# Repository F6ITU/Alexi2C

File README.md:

# Alexi2C

Kicad files

I2C control board interfacing 
Alexiares/Penelope input/output filter set 
with Hermes Lite 2.x & Red Pitaya 

It could also be used with a decimal/7 bits binary input for 
Hermes lite 1.0 

http://www.hermeslite.com/

This board is a fork of the DC2PD interface for the Red Pitaya
http://rz1zr.ru/files/Hermes_and_Alex_outputs.pdf

It has
been designed to 

- Control a set of Alexiares LPF and HPF filters
using the Hermes lite or Red Pitaya's I2C output (Steve KF7O or Pavel Denim's firmware).
http://pavel-demin.github.io/red-pitaya-notes/sdr-transceiver-hpsdr/

- Control a simple BCD or decimal filter (J6 output of an Hermes Lite)
In this case, the TCA9555 and the 5 pins "I2C Input" connector are not used

 === Hardware modifications===

A set of darlington (ULN2803) is used to fit the voltage 
and current requirement of both lpf and hpf boards. 

A pair of jumpers located close to the output connectors 
allow to use the "local" 12V  power rail if set, 
or any external voltage when opened. 

For hams using this board with the KF7O's Hermes Lite V1 (deprecated dev.), two connectors 
have been added to directly control the drivers in decimal mode,
thus to control a Penelope, Alexiares or an Alex SV1AL softrock based 
"Big Mobo" filter set ( or any filter 
board using negative logic band switching) 

Please note that the antenna and attenuator commands need a separate 
board if an Alex lpf/hpf filter set is already used (Pavel's firmware). 

An antenna switching board project could be downloaded and/or forked from 

https://github.com/F6ITU/Alexiares_Coax_Out

(attenuators are integrated on the HPF filter board, under design)

When using AlexI2C, Alexandrie control board, the original I2S interface

https://github.com/F6ITU/Alexandrie

should NOT be used (it seems obvious, but who knows...)

AlexI2C acts as an "almost complete" substitute of the original board and is 
dedicated to people who don't want to use Alexiares's I2S protocol.

3D image of the board are stored on this repo

Alexi2C dwn.jpg

Alexi2C up.jpg

Board's dimensions are oversized to fit the 5x10 and 10x10cm 
size of all board of the Hermes project under Kicad: 

AlexI2C

Alexandrie 

Alexiares_Coax_Out

Alexiares_HPF

Alexiares_LPF

Mentor

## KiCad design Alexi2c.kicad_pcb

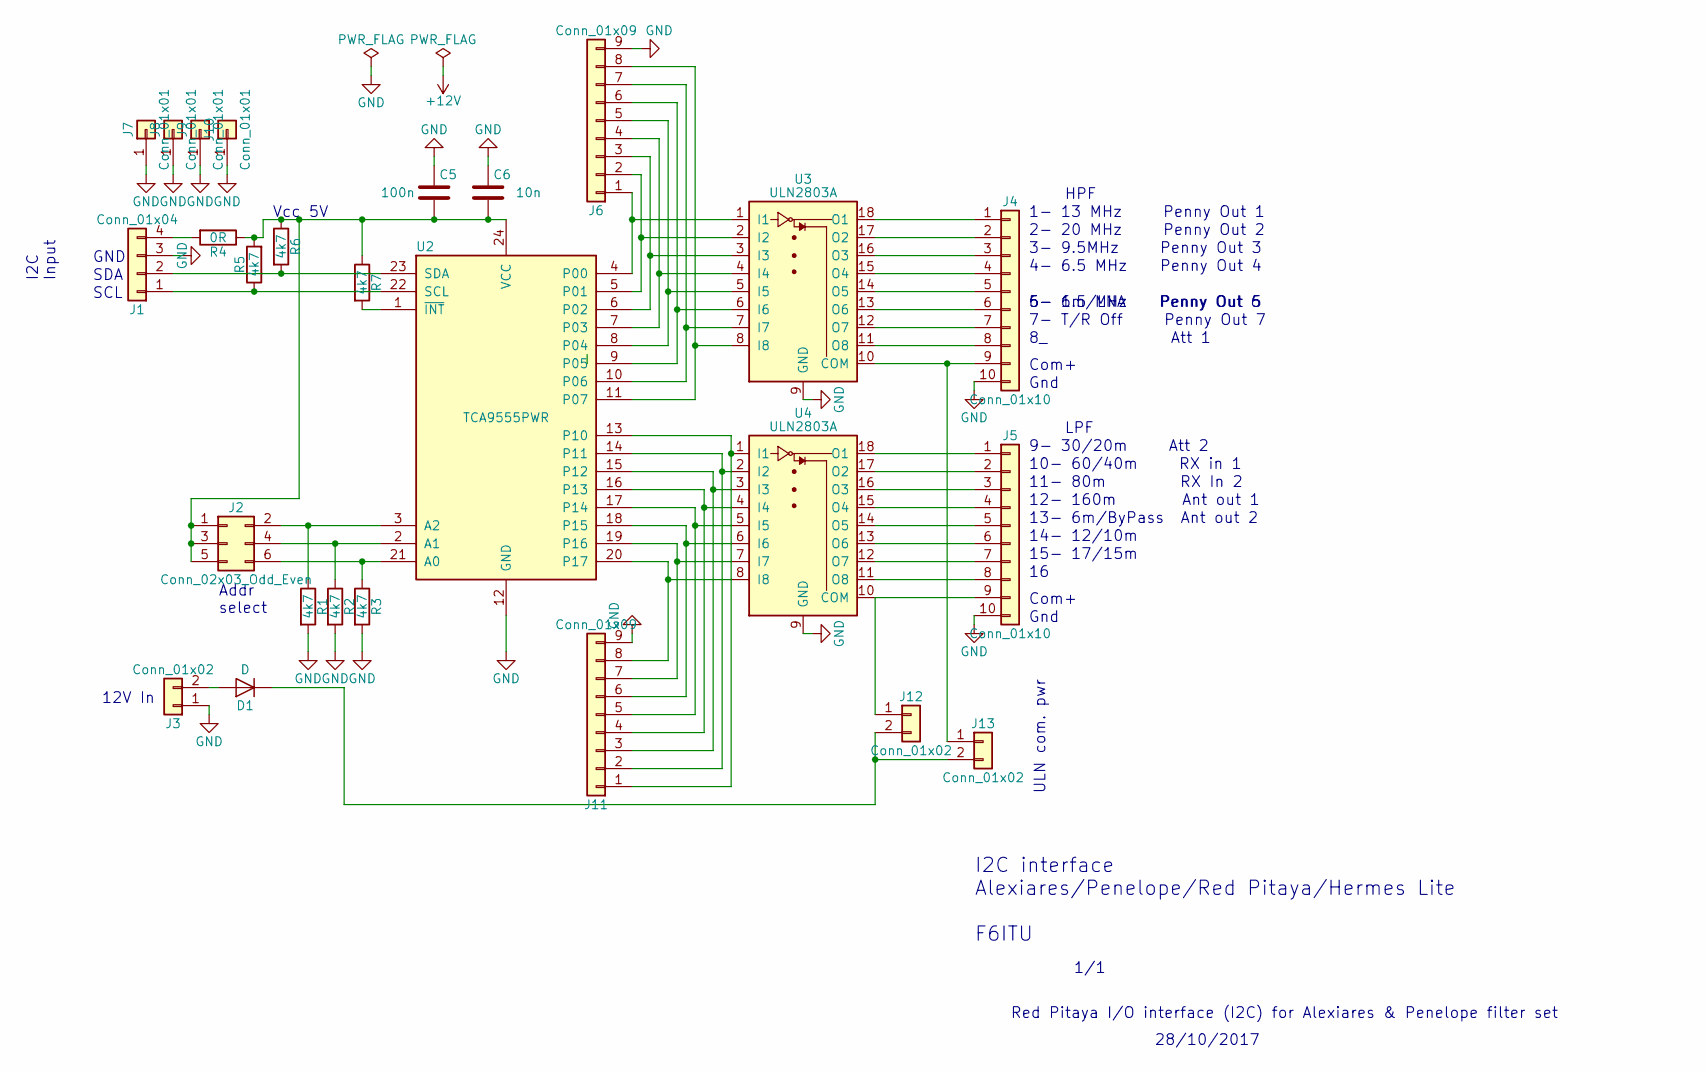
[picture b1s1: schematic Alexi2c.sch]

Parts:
C5: 100n; C_0805_HandSoldering
C6: 10n; C_0805_HandSoldering
D1: D; D_2010
J1: Conn_01x04; kk100_22-23-2041
J2: Conn_02x03_Odd_Even; Pin_Header_Straight_2x03_Pitch2.54mm
J3: Conn_01x02; kk100_22-23-2021
J4, J5: Conn_01x10; kk100_22-23-2101
J6, J11: Conn_01x09; kk100_22-23-2091
J7, J8, J9, J10: Conn_01x01; MountingHole_3.2mm_M3_ISO14580_Pad
J12, J13: Conn_01x02; Pin_Header_Straight_1x02_Pitch2.54mm
R1, R2, R3, R5, R6, R7: 4k7; R_0805_HandSoldering
R4: 0R; R_0805_HandSoldering
U2: TCA9555PWR; TSSOP-24_4.4x7.8mm_Pitch0.65mm
U3, U4: ULN2803A; SOIC-18W_7.5x11.6mm_Pitch1.27mm

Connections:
GND: C5.1, C6.1, J1.3, J3.1, J4.10, J5.10, J6.9, J7.1, J8.1, J9.1, J10.1, J11.9, R1.2, R2.2, R3.2, U2.12 (GND), U3.9 (GND), U4.9 (GND)
unnamed: C5.2, C6.2, J2.1, J2.3, J2.5, R4.1, R5.2, R6.1, R7.1, U2.24 (VCC)
unnamed: D1.1 (K), J12.2, J13.2
unnamed: D1.2 (A), J3.2
unnamed: J1.1, R5.1, U2.22 (SCL)
unnamed: J1.2, R6.2, U2.23 (SDA)
unnamed: J1.4, R4.2
unnamed: J2.2, R1.1, U2.3 (A2)
unnamed: J2.4, R2.1, U2.2 (A1)
unnamed: J2.6, R3.1, U2.21 (A0)
unnamed: J4.1, U3.18 (O1)
unnamed: J4.2, U3.17 (O2)
unnamed: J4.3, U3.16 (O3)
unnamed: J4.4, U3.15 (O4)
unnamed: J4.5, U3.14 (O5)
unnamed: J4.6, U3.13 (O6)
unnamed: J4.7, U3.12 (O7)
unnamed: J4.8, U3.11 (O8)
unnamed: J5.1, U4.18 (O1)
unnamed: J5.2, U4.17 (O2)
unnamed: J5.3, U4.16 (O3)
unnamed: J5.4, U4.15 (O4)
unnamed: J5.5, U4.14 (O5)
unnamed: J5.6, U4.13 (O6)
unnamed: J5.7, U4.12 (O7)
unnamed: J5.8, U4.11 (O8)
unnamed: J6.1, U2.4 (P00), U3.1 (I1)
unnamed: J6.2, U2.5 (P01), U3.2 (I2)
unnamed: J6.3, U2.6 (P02), U3.3 (I3)
unnamed: J6.4, U2.7 (P03), U3.4 (I4)
unnamed: J6.5, U2.8 (P04), U3.5 (I5)
unnamed: J6.6, U2.9 (P05), U3.6 (I6)
unnamed: J6.7, U2.10 (P06), U3.7 (I7)
unnamed: J6.8, U2.11 (P07), U3.8 (I8)
unnamed: J11.1, U2.13 (P10), U4.1 (I1)
unnamed: J11.2, U2.14 (P11), U4.2 (I2)
unnamed: J11.3, U2.15 (P12), U4.3 (I3)
unnamed: J11.4, U2.16 (P13), U4.4 (I4)
unnamed: J11.5, U2.17 (P14), U4.5 (I5)
unnamed: J11.6, U2.18 (P15), U4.6 (I6)
unnamed: J11.7, U2.19 (P16), U4.7 (I7)
unnamed: J11.8, U2.20 (P17), U4.8 (I8)
unnamed: J5.9, J12.1, U4.10 (COM)
unnamed: J4.9, J13.1, U3.10 (COM)
unnamed: R7.2, U2.1 (~INT)

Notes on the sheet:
12V In
Addr select
I2C Input
I2C interface Alexiares/Penelope/Red Pitaya/Hermes Lite F6ITU
SDA
SCL
GND
Vcc 5V
1- 13 MHz Penny Out 1
2- 20 MHz Penny Out 2
3- 9.5MHz Penny Out 3
4- 6.5 MHz Penny Out 4
5- 1.5 MHz Penny Out 5
6- 6m/LNA Penny Out 6
7- T/R Off Penny Out 7
8_ Att 1
9- 30/20m Att 2
10- 60/40m RX in 1
11- 80m RX In 2
12- 160m Ant out 1
13- 6m/ByPass Ant out 2
14- 12/10m
15- 17/15m
Com+
Gnd
HPF
LPF
1/1
28/10/2017
Red Pitaya I/O interface (I2C) for Alexiares & Penelope filter set
ULN com. pwr

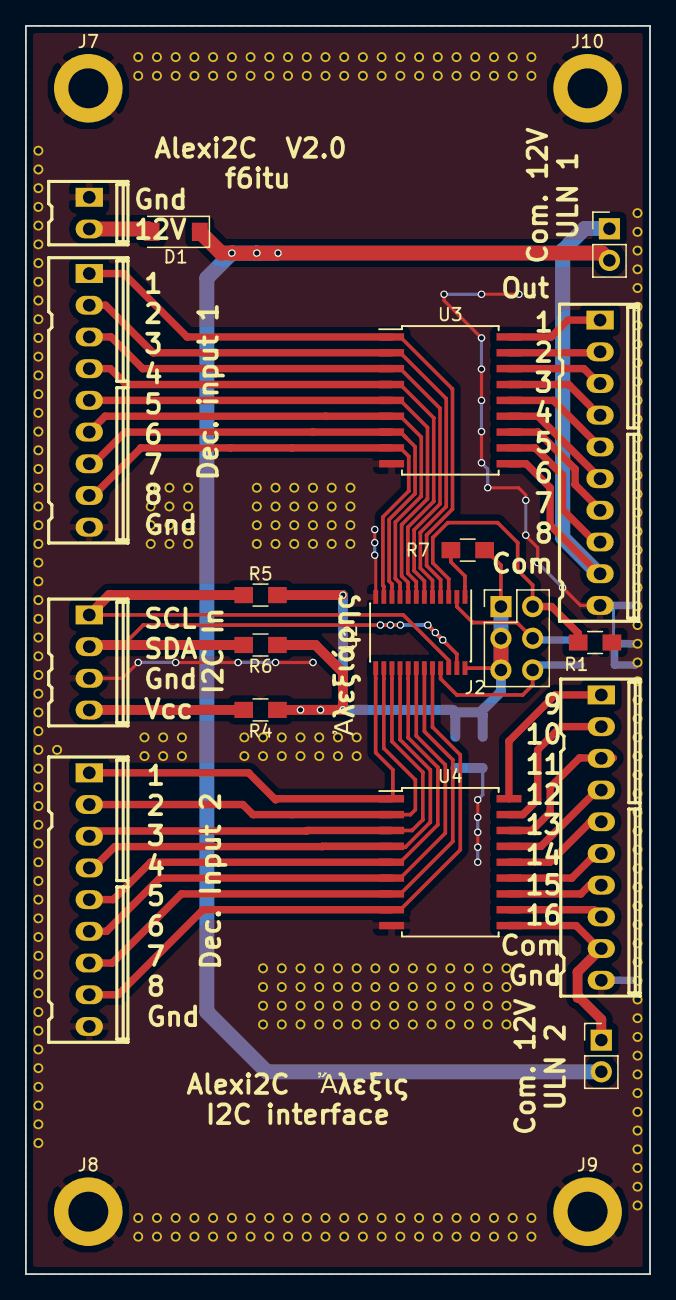
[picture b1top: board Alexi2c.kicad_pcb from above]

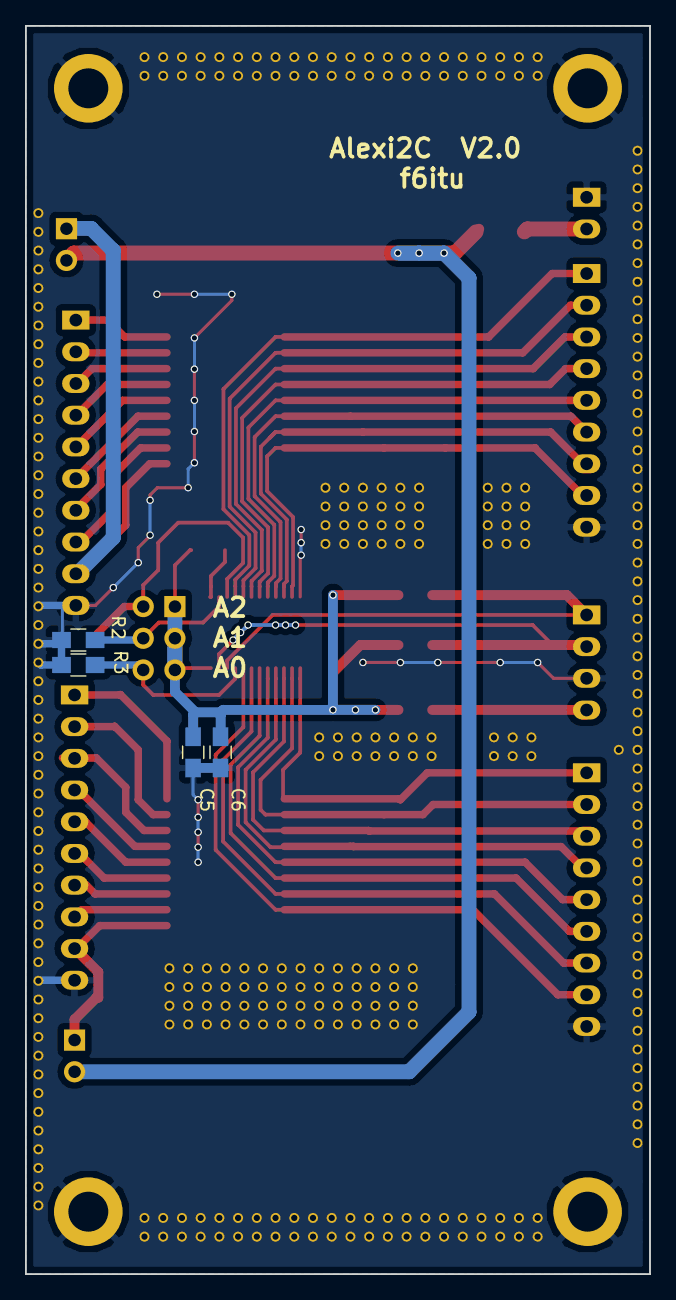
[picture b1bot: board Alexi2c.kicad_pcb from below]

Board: 2 copper layers, 50.0 x 100.0 mm, 26 parts (4 on the bottom side), 45 nets.

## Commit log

2017-11-01 RTM 1
2017-11-02 Readme cleanup
2017-11-27 new I2C decoder module
2017-12-03 README change
2017-12-22 added protec. diode, I2C Pull-up, I2C Vdd strap
2017-12-30 image and BOM added, minor changes
2017-12-30 Gerber files added
2018-07-05 new stitching, minor silkmask mods
2018-07-23 Alexi2C V2.0 RTM
2019-03-15 upgrate to Kicad 5.0n, new up to date Gerber
